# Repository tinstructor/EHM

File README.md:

# EHM
An energy harvester with advanced monitoring capabilities.

## Table of Contents
<!-- TOC -->

  - [About The Project](#about-the-project)
  - [Getting Started](#getting-started)
    - [Cloning the EHM Repository](#cloning-the-ehm-repository)
    - [Installing Autodesk EAGLE](#installing-autodesk-eagle)
    - [Navigating the Project Files](#navigating-the-project-files)
    - [Generating Gerber Files](#generating-gerber-files)
  - [Hardware Configuration](#hardware-configuration)
    - [Ordering PCB's](#ordering-pcbs)
    - [Sourcing Components](#sourcing-components)
    - [Soldering](#soldering)
  - [Device Operation](#device-operation)
    - [Energy Harvester](#energy-harvester)
    - [Current Sense Amplifiers](#current-sense-amplifiers)
    - [Voltage Buffer](#voltage-buffer)
    - [Power Delivery](#power-delivery)
    - [ADC](#adc)
    - [Solder Bridges](#solder-bridges)
  - [License](#license)

<!-- /TOC -->

## About The Project

This project was created with [Autodesk EAGLE](http://eagle.autodesk.com/)

## Getting Started

### Cloning the EHM Repository

In order to download the source files in a zip archive, click [here](https://github.com/tinstructor/EHM/archive/master.zip). Alternatively you may also clone this repository using git bash terminal commands. Substitute "John Doe" by your own username and use your own email address.

```bash
$ git config --global user.name "John Doe"
$ gif config --global user.email "john.doe@example.com"
```

Next up, enter the following command to clone the repository into the folder in which you opened the git bash terminal. Choose your location conveniently, for example `C:\Users\<username>\Documents\EAGLE\repos` might be a good place.

```bash
$ git clone https://github.com/tinstructor/EHM.git
```

From here on I'll assume all directies to be relative to whatever directory you chose to clone the project in. Also, I'll be using Windows style backslash notations because I just happened to be writing this on a Windows machine. If that offends you, you should really grow up.

### Installing Autodesk EAGLE

Once you've cloned the repository and thereby obtained the necessary files, a free version of Autodesk EAGLE may be downloaded from [here](https://www.autodesk.com/products/eagle/free-download). This is not some trial version that prompts you to spend money you really don't have, instead it is a limited version of the software meant for hobbyists. For our intents and purposes the features offered by the hobbyist version are more than adequate.

>**Note:** if you're a student or an educator you may apply for an educational license [here](https://www.autodesk.com/education/free-software/eagle), which grants you access to the full version of the latest EAGLE release, albeit for non-profit use only.

### Navigating the Project Files

When opening EAGLE for the first time, navigate to the `Options > Directories` tab in the top-left corner. A pop-up window will appear. It is here that you must now add the location of the project files in order to open them in EAGLE. Go to the `Projects` field and add the absolute location of the `EHM\Project` folder, seperating it from the default project location with a semicolon `;`.

The project files will now appear in the control panel view. Notice that there are 2 files present, i.e., a schematic and a board file. Double clicking either of these files will cause both of them to open simultaneously in a seperate window. It is imperative that you always have both file windows open at the same time when making changes of any type. Otherwise you may run into horrible inconsistency problems. No worries, if you where to accidently close one of these windows, EAGLE will prompt you with a bright yellow and black banner.

Learning to use EAGLE efficiently may seem difficult in the beginning but it's not actually that bad. In fact Autodesk has some nice [tutorials](https://www.autodesk.com/products/eagle/blog/?s=schematic+basics) that'll get you going in no time.

### Generating Gerber Files

In case you've made changes to the board layout, you'll need to generate new Gerber files. These files tell the machines of your PCB manufacturer of choice how to lay out all traces and other stuff exactly how you designed it. In order to do this, open the board layout window and navigate to the `File > CAM Processor` tab.

A pop-up window now appears. The process of generating gerber files is clearly demonstrated in [this video](https://youtu.be/Jf2y1rTRHDg). However, I've spared you some extra steps and created a simple cam job file `gerb274x.cam` (located in `EHM\CAM`) for you to load as follows:

After browsing the file explorer and choosing the appropriate CAM file, all you need to do is press the `Process Job` button in the bottom-right corner of the CAM Processor pop-up window. This will generate a new zip archive called `Gerber.zip` in the `EHM\Project` folder. If you didn't make any changes, a handy `Gerber.zip` archive is already located in the repository folder itself (`EHM\Gerber.zip`).

## Hardware Configuration

### Ordering PCB's

Now, when it comes to ordering PCB's there are a stupid amount of manufacturers out there and they're all claiming some perceived advantage over their competitors. Let me tell you, for the most part it's all marketing b\*llsh\*t. Which manufacturer you choose typically depends on price, manufacturing capabilities and how fast they can deliver. For hobbyists like you and me, the latter is typically of less importance while we tend to focuss more on low pricing.

These days, when I order relatively small dual-layer PCB's for prototyping purposes I'll typically order from [JLCPCB](https://jlcpcb.com/). For the price their manufacturing capabilities and quality are outstanding. In fact, you'll have a hard time finding better prices regardless off  manufacturing capabilities. I mean, €7.06 (before shipping) for 10 PCB's and a stencil is somewhat unreal.

>**Note:** choosing a lead-free finish will add €5.30 to the total price. However, since most hobbyist solder with leaded solder anyway, you must ask yourself whether shelling out extra money for a small batch of prototypes is worth it.

A great way to save some cost in the long run while making your job easier is to use a stencil printer like the [CYBRES SP2421](https://www.tindie.com/products/CYBRES/cybres-sp2421-stencil-printer/) or the [NeoDen PM3040](https://printtec.nl/contents/nl/d361.html). The purpose of a stencil printer will become clear in the section on [Soldering](#soldering). What you need to know at this stage is that there are two types of (manual) stencil printers: while the SP2421 requires no stencil frame (where the PM3040 does) it does require a set of precision cut holes in your stencil. If you've got the capabilities to cut these holes and do it precisely, it's a great way to save some money on both the printer itself as well as the additional shipping costs associated with framed stencils.

>**Note:** stencil jigs typically accept stencils with a maximum size. Make sure to set the size of the stencil accordingly when ordering! Setting a custom stencil size comes with no additional cost, at least on [JLCPCB](https://jlcpcb.com/) it doesn't.

### Sourcing Components

First of all, let me state that sourcing components for absolute bottom dollar (or euro in my case) may well be considered a black art. My advise would be to get what you can on [LCSC](https://lcsc.com/) and have them ship your order together with your PCB's from [JLCPCB](https://jlcpcb.com/). That way you can avoid additional shipping fees.

Since the component selection on LCSC is somewhat limited you could go to places like [Mouser](https://www.mouser.com/) for the miscellaneous stuff like the BQ25570RGRR energy harvesting IC and the MAX9934TAUA+ current sense amplifier.

~~Anyway, at the time of writing this, I wasn't sure yet as to which type of energy I'd be harvesting (solar, thermal, ...) so I couldn't really give you a Bill Of Materials (BOM).~~ However, since most critical components are marked in the schematic with their full partname I'm sure you'll have no trouble obtaining the correct components if you really wanted to. My advice would be to always make sure you get the part with the correct footprint.

>**Note:** make sure to order y14870rxxx00b9r type current resistors with a CSM2512 footprint as illustrated in `EHM\Datasheets\y14870rxxx00b9r.pdf`.

Oh yeah and before I forget, sites like [Banggood](https://www.banggood.com/) are amazing for getting pre-assembled cables like [this](https://www.banggood.com/100Pcs-Mini-Micro-JST-1_0mm-SH-2-Pin-Connector-Plug-With-Wires-Cables-150mm-p-1170285.html) one and [this](https://www.banggood.com/20Pcs-Mini-Micro-JST-1_0mm-SH-6-Pin-Connector-Plug-With-Wires-Cables-150mm-p-1170259.html) one. What's more, Banggood typically charges completely nothing for shipping. The only downside is that stuff will take some weeks to arrive at your doorstep. That's what you get for being so cheap.

### Soldering

While we're on the subject of Banggood, they have a pretty awesome selection of soldering supplies. I myself am a big fan of offerings from [Mechanic](https://www.banggood.com/search/mechanic-solder.html) and of their [XG-Z40](https://www.banggood.com/XG-Z40-10cc-Syringe-Solder-Paste-Flux-Paste-Sn63Pb37-25-45um-p-973158.html) solder paste syringe in particular. If you have no morality issues with leaded solder and you want to spend less money and time on soldering, XG-Z40 is the way to go.

>**Note:** when buying solder paste in a syringe (like the XG-Z40) you'll also need some [blunt tip needles](https://www.banggood.com/search/blunt-tip-fill-needle.html). Make sure to choose tips with a sufficiently large diameter. Otherwise you'll have a hard time pushing out solder paste. My advice is to go with 0.9mm diameter (typically pink) ones. You'll also need to plan a trip to your local pharmacy to get some [10ml syringes](https://www.farmaline.be/apotheek/bestellen/wegwerpspuit-10-ml-terumo-zonder-naald-ss-10es/) because you'll need the rubber plunger thingy in order to push the solder out of the syringe.

While XG-Z40 is fine for small rework purposes (as shown in [this](https://youtu.be/4Z1B_DbW-C0) video), when using a stencil you'd really need some [solder paste](https://www.banggood.com/MECHANIC-Soldering-Solder-Welding-Paste-Flux-SMD-SMT-Sn63Pb37-Tool-Soldering-Iron-Flux-Repair-Tool-p-1328894.html) in a jar. Numerous tutorials are available on how to start using stencils for solder paste dispension. For example [this](https://www.youtube.com/watch?v=WDIqtGMROjM) video from Sparkfun is a great place to start when you don't have the funds for an expensive stencil printer. If you do however (have such funds), [this](https://youtu.be/ud8odsM8eA4) video shows how its done.

After putting solder paste on your board and carefully sticking the component to it, you have several different options for heating the solder paste so that it may eventually solidify. For example, you could hit it with a [hot air station](https://www.reichelt.com/be/en/digital-hot-air-smd-rework-station-320w-esd-station-zd-939l-p161632.html). Hot air stations are relatively cheap compared to other solutions and besides, they are an irreplaceable shop tool. Another cheap-ish option is a [hot plate](https://www.tindie.com/products/LafrasH/modern-electronics-reflowr-v2/). The problem with it is that it really only works well for one side of your PCB, which would require you to manually solder components to the pads on the opposite side of the PCB with a hot air gun and/or a conventional soldering iron (with some special tips). Nonetheless this may prove useful if you've placed the most difficult to solder components on the same side. A much more powerful and vastly more expensive solution is something like a
[vapour phase reflow oven](https://www.eleshop.nl/vapour-phase-soldeeroven-mini-condens-it.html).

>**Note:** some people even use conventional electrically heated skillets or toaster ovens. While these methods are inexpensive, they tend to heat your PCB unevenly, potentially causing spotburns and/or tombstoning. The same can be said about the IR reflow ovens of yesteryear.

## Device Operation

### Energy Harvester

According to the design principles and other useful information laid out in `EHM\Datasheets\bq25570.pdf` and `EHM\Literature\sluuaa7a.pdf`, the BQ25570 IC allows for a number of configurations to be made pertaining to its operation. But before we can start you might be wondering, what exactly is the function of this chip? The following quote should start to make things somewhat clear:

> *"The bq25570 device is a highly integrated energy harvesting Nano-Power management solution that ... is specifically designed to efficiently acquire and manage the microwatts (µW) to milliwatts (mW) of power generated from a variety of DC sources like photovoltaic (solar) or thermal electric generators. \[It is\] targeted toward products and systems, such as wireless sensor networks (WSN) which have stringent power and operational demands."* <br/>
>
> **Texas Instruments**

In order to do this, the capabilities of the BQ25570 are twofold. First of all, it contains a boost charger whose intended purpose is to boost the low voltage output of harvesters such as small solar cells or a Thermo-Electric Generator (TEG) (connected to J2) to a constant voltage level that is sufficiently high to charge a storage element connected to the battery terminal J4. It does this as efficiently as possible by means of a mechanism called Maximum Powerpoint Tracking (MPPT). The purpose of MPPT is to match the input impedance of the boost charger to the output impedance of the energy harvester which in turn ensures a maximum transfer of power.

>**Note:** if you want to know more about how MPPT works I suggest you have a look at `EHM\Literature\erbay2014.pdf` and `EHM\Literature\kong2012.pdf`.

More specifically, in this case, the integrated MPPT block continuously measures a certain user configurable percentage (i.e., the MPPT percentage) of the energy harvester's open circuit voltage and uses this information to control the switching frequency of the boost converter to match its input impedance to be equal to the harvester's output impedance, thus assuring maximum power transfer. Choosing the MPPT percentage depends heavily on the type of energy harvesting device. If its output impedance is purely resistive, setting the MPPT percentage to 50% (VOC_SAMP = GND) ensures maximum power transfer. However, the capacitive nature of a solar cell's output impedance requires an MPPT percentage closer to 80% (VOC_SAMP = VBAT). For your convenience I've also added the possibility to set a custom MPPT percentage by means of a resistor divider consisting of (R20 + R21) and R22.

Switching the MPPT percentage between 50% (VOC_SAMP = GND), 80% (VOC_SAMP = VBAT) or a custom value can be done by setting a jumper (see picture below) to the corresponding position on JP1. The same connector (JP1) also provides the ability to either enable or disable the entire chip by tying the NEN input of the IC to GND or VBAT respectively.

That being said, certain requirements need to be met before the main boost charger (with the aforementioned impedance matching capabilities) is operational. More specifically, when VSTOR < VSTOR_CHGEN (= 1.8V) the IC operates in cold-start mode. The cold-start circuit is essentially an unregulated, hysteretic boost converter with lower efficiency compared to the main boost charger. None of the other features function during cold start operation.

>**Note:** `EHM\Literature\kong2012.pdf` explains in great detail why a cold start cirquit might be necessary.

The cold start circuit's goal is to charge the voltage on CSTOR (i.e., VSTOR) higher than VSTOR_CHGEN so that the main boost charger can operate. When the VSTOR voltage reaches VSTOR_CHGEN, the main boost charger starts up. Once the VSTOR pin voltage goes above VBAT_UV (1.95V) plus the VBAT_UV_HYST threshold (15mV), the VSTOR pin and VBAT pins are effectively shorted through an internal PMOS FET. The switch remains closed until the VSTOR pin voltage falls below the VBAT_UV threshold. The VBAT_UV threshold should be considered a fail safe to the system and the system load should be removed or reduced based on the user-configurable VBAT_OK threshold which should be set above the VBAT_UV threshold.

To prevent rechargeable batteries from being exposed to excessive charging voltages and to prevent over charging a capacitive storage element, the over-voltage (VBAT_OV) threshold level must be set using external resistors (see following equation). This is also the voltage value to which the charger will regulate the VSTOR/VBAT pin when the input provides sufficient power. The VBAT_OV threshold when the battery voltage is rising is given by:

The overvoltage threshold when battery voltage is decreasing is given by VBAT_OV minus VBAT_OV_HYST (24mV). Once the voltage at the battery exceeds the VBAT_OV threshold, the boost charger is disabled. The charger will start again once the battery voltage drops VBAT_OV_HYST.

The charger allows the user to set a programmable voltage independent of the overvoltage and undervoltage settings to indicate whether the VSTOR voltage (and therefore the VBAT voltage when the PFET between the two pins is turned on) is at an acceptable level. When the battery voltage is decreasing the threshold is set by:

When the battery voltage is increasing, the threshold is set by:

The logic high level of this signal (i.e., the VBAT_OK output) is equal to the VSTOR voltage and the logic low level is GND. Figure 21 taken from `EHM\Datasheets\bq25570.pdf` shows the relative position of the various threshold voltages discussed so far.

Anyway, apart from boosting the voltage of an energy harvester, the BQ25570 also contains a buck converter. The buck converter input is internally connected to VSTOR and steps the VSTOR voltage down to a lower regulated voltage at the OUT connector (J1 and J3). It employs pulse frequency modulation (PFM) control to regulate the voltage close to the desired reference voltage. The voltage regulated at the OUT pin is set by a user programmable resistor divider according to the following equation:

Connector JP2 allows you to configure the behaviour of the buck converter output. According to the BQ25570 datasheet (`EHM\Datasheets\bq25570.pdf`), if you tie VOUT_EN to VSTOR, the buck converter is disabled when the voltage on VSTOR drops below the VBAT_UV condition. The buck converter continues to operate in pass (100% duty cycle) mode, passing the input voltage to the output, as long as VSTOR is greater than VBAT_UV and less than VOUT. However, it fails to make clear the true functionality of the VOUT_EN input. You see, when reading `EHM\Literature\sluuaa7a.pdf`, it becomes evident that connecting VOUT_EN to VBAT_OK makes it so that the buck converter is turned off when VSTOR < VBAT_OK (when VSTOR is decreasing) or if VSTOR < VBAT_OK_HYST (when VSTOR increases). Connecting VOUT_EN to GND turns off the buck converter entirely.

The `EHM\BQ25570_Design_Help_V1_3.xlsx` spreadsheet is a handy tool that calculates a set of resistor values that fits best within the operational constraints provided by you, the user. For your convenience I've provided you with some values that reflect a common scenario wherein a single cel Li-Ion battery or a dual cell NiMH battery are used as a storage element in conjunction with, e.g., a small solar cell (with an output voltage ≤ 3.5V) such as [this](https://www.banggood.com/0_36W-2V-42_548_53mm-Solar-Panel-Epoxy-Board-with-Wire-p-1369156.html?rmmds=search&cur_warehouse=CN) one or [this](https://www.gearbest.com/other-accessories/pp_009728526124.html) one (when space is limited) or [this](https://www.banggood.com/3_5V-250mA-0_8W-Mini-Epoxy-Solar-Panel-Photovoltaic-Panel-p-987778.html?rmmds=search&cur_warehouse=CN) one when device footprint is no issue.

>**Note:** the MPPT percentage (40%) is just for demonstration purposes in this case. Solar panels work best when the MPPT percentage is set to approximately 80%.

Choosing an appropriately sized solar panel and storage element (most likely a 3.7V battery) is not an easy feat and depends heavily on your use case. Luckily I've provided another handy spreadsheet (`EHM\bq25570SolarAppDesignExample_V1p3.xlsx`) which accepts a number of parameters and calculates the required size of your solar panel as well as the minimum battery capacity required (given a nominal voltage). I've loaded the spreadsheet with some parameters that reflect the absolute worst case scenario for a sensor node that uses every possible function of the hardware (including chips other than the BQ25570) to repeatedly send a message every 60 seconds.

>**Note:** seriously, even if you tried you wouldn't be able to design a **sensor** node setup with a worse performance than the one laid out in `EHM\bq25570SolarAppDesignExample_V1p3.xlsx`. Except maybe if you used IEEE 802.11 links or something funny like that.

All resistors are E96 series 1% resistors with an 0603 footprint. The following table provides a summary of the proposed configuration and the passive components required:

I strongly recommend you to read `EHM\Datasheets\bq25570.pdf` for additional design considerations, e.g., regarding the appropriate sizing of several capacitors, etc.

### Current Sense Amplifiers

If the purpose is to monitor both input and output power, you'd need to measure both input and output current (as well as voltage). Hence, a shunt resistor was added to both the input and output, each in combination with a MAX9934TAUA Current Sense Amplifier (CSA). This device amplifies the voltage drop across the shunt resistance before it may be measured by an Analog to Digital Converter (ADC). If I hadn’t use a CSA, the voltage difference would either be too small to measure or you'd need to make the shunt resistor very big, leading to unacceptable power losses.

The MAX9934TAUA is an interesting CSA in that it behaves as a current-source with a transconductance . Thus, by pulling its output to GND with a sufficiently large resistor (let's call it  for now) we are able to adjust the voltage gain  according to the following equation:

Let's say you'd want to use an ADC with a resolution of 10 bits. At this resolution there are  levels ranging from 0V to the VOUT of the buck converter (2.7V if you used the proposed configuration). The following equation shows how one could calculate the measured voltage given an output value x of the ADC:

In our case, the smallest measurable voltage delta (by the ADC) equals . Now, assume we want to measure the current through the input shunt resistor with a resolution of 200µA, then the smallest possible voltage gain may be obtained from the following equation:

However since the ADC input only ranges to VOUT of the buck converter, there's also a maximum possible voltage gain. Let's say the maximum input current of the boost charger equals 200mA (which is well within the specs stated in `EHM\Datasheets\bq25570.pdf`), then the following equation puts an upper limit to the voltage gain:

>**Note:** you could easily calculate that in fact, the shunt resistor is not the limiting factor when it comes to resolution. In all cases  must hold true. By assuming the resolution is unknown this comes down to: <br/>
>
>  <br/>
>
> 

A trade-off now presents itself. The larger the shunt resistance, the lower the voltage gain and the less influence small (tolerance) deviations have on the measurement. However, a larger shunt resistor also equates to more power loss. Let's say that a shunt resistor of 50mΩ does the trick. Assuming the measurement resolution equals 200µA, the voltage gain must be somewhere in the range of . The corresponding output termination resistor () can then be calculated as follows:

Therefore . I strongly encourage the use of a 10.7kΩ 0.1% 0603 resistor like the one found in `EHM\Datasheets\era-3aeb1072v.pdf`. This offering from Panasonic is extremely precise. In that case the voltage gain equates to:

>**Note:** calculating the current is now simply a matter of dividing a measurement obtained from the ADC by the known gain and shunt resistor values (in software).

The output shunt resistor employs the same principles. However, according to `EHM\Datasheets\bq25570.pdf`, the maximum output current of the buck converter equals 110mA. Therefore, the following equation must hold true:

Again, in all cases  must hold true. By assuming the resolution to be an unknown variable x this comes down to:

 <br/>

Let's say a resolution of 110µA is adequate for our purposes and a shunt resistor of 100mΩ does the trick. Then, the voltage gain must be somewhere in the range of . Thus . I strongly encourage the use of a 9.76kΩ 0.1% 0603 resistor like the one found in `EHM\Datasheets\era-3aeb9761v.pdf`. This offering from Panasonic is extremely precise. In that case the voltage gain equates to:

>**Note:** due to footprint requirements, the only possible shunt resistors are specified in `EHM\Datasheet\y14870rxxx00b9r.pdf`. For example, in the above case, you'd need to order the Y14870R10000B9R and Y14870R05000B9R variants.

For your convenience I've added a spreadsheet in `EHM\CSA_help.xlsx` that combines all these calculations. This allows you to properly configure your current sense amplifiers based on the precision of your ADC (expressed as N bits) as well as the transconductance of the CSA and the output voltage (i.e., the positive rail of the ADC) of the bq25570 buck converter output. For example (see image below), with a 12 bit ADC one could increase the current measurement resolution significantly, at the cost of increased power consumption inherent to a more precise ADC that is. 

### Voltage Buffer

The input resistance and capacitance of an ADC input are typically chosen to accomodate most common scenarios. However, when dealing with particularly small currents and voltages it is common to buffer these inputs for all sorts of reasons. Moreover, it is considered good practice to filter out spurious high frequency compoments at the ADC inputs because otherwise they might be replicated in the frequency spectrum after sampling and distort your measurements (think Shannon-Nyquist theorem). According to the principles laid out in `EHM\Literature\tidu390.pdf` and the information obtained from `EHM\Datasheets\ads7041.pdf`, a buffer-filter combination consisting of an `EHM\Datasheets\opa314.pdf` op-amp and low pass RC filter with  and  was chosen.

>**Note:** both `EHM\Literature\tidu390.pdf` and `EHM\Datasheets\ads7041.pdf` stress the importance of using an NOG type ceramic capacitor for  over a common XR7 type capacitor since these may yield spurious frequency harmonics due to the fact that their actual capacitance value is typically temperature dependent.

>**Note:** since , the sampling rate should be at least 1 MSPS in order to comply with the Shannon-Nyquist sampling theorem, and ideally even higher since no analog filter is infinitely steep.

All signals that are to be sampled are multiplexed onto a single line just before the buffer-filter input with a `EHM\Datasheets\dg2034e.pdf` low rds-on 4 channel MUX. Since the input impedance of the buffer is very high, the additional resistance introduced by the MUX shouldn't result in significant attenuation of the signals. The following thruth table lists which input (denoted with S) is switched to the output according to the logical signal level on the A0 and A1 inputs.

When properly configured (by means of the appropriate solder bridges) S1 is connected to the (divided) input signal  of the bq25570 boost charger, i.e., the positive terminal of connector J2. In similar fashion, S2 is connected to the (divided) positive output of the connected storage element  while S3 is connected to the output of the CSA measuring the bq25570 buck converter output current and S4 is connected to the output of the CSA measuring the bq25570 boost charger input current. The following image shows the location of connector J7, which contains the A0 and A1 inputs. 

Because the battery and input voltage may be greater than the MUX, buffer and ADC supply voltage, I've added the possibility to divide the corresponding MUX input voltages by means of a resistor divider. It is advisable to go with large resistance values so as to minimize power losses. Something like the 10MΩ 0.5% 0603 resistors from `EHM\Datasheets\crcw060310m0dheap.pdf` are an exellent choice.

### Power Delivery

Coming soon

### ADC

Coming soon

### Solder Bridges

Coming soon

## License
This project and all original material included with it are released under [CC BY-SA 3.0](https://creativecommons.org/licenses/by-sa/3.0/)

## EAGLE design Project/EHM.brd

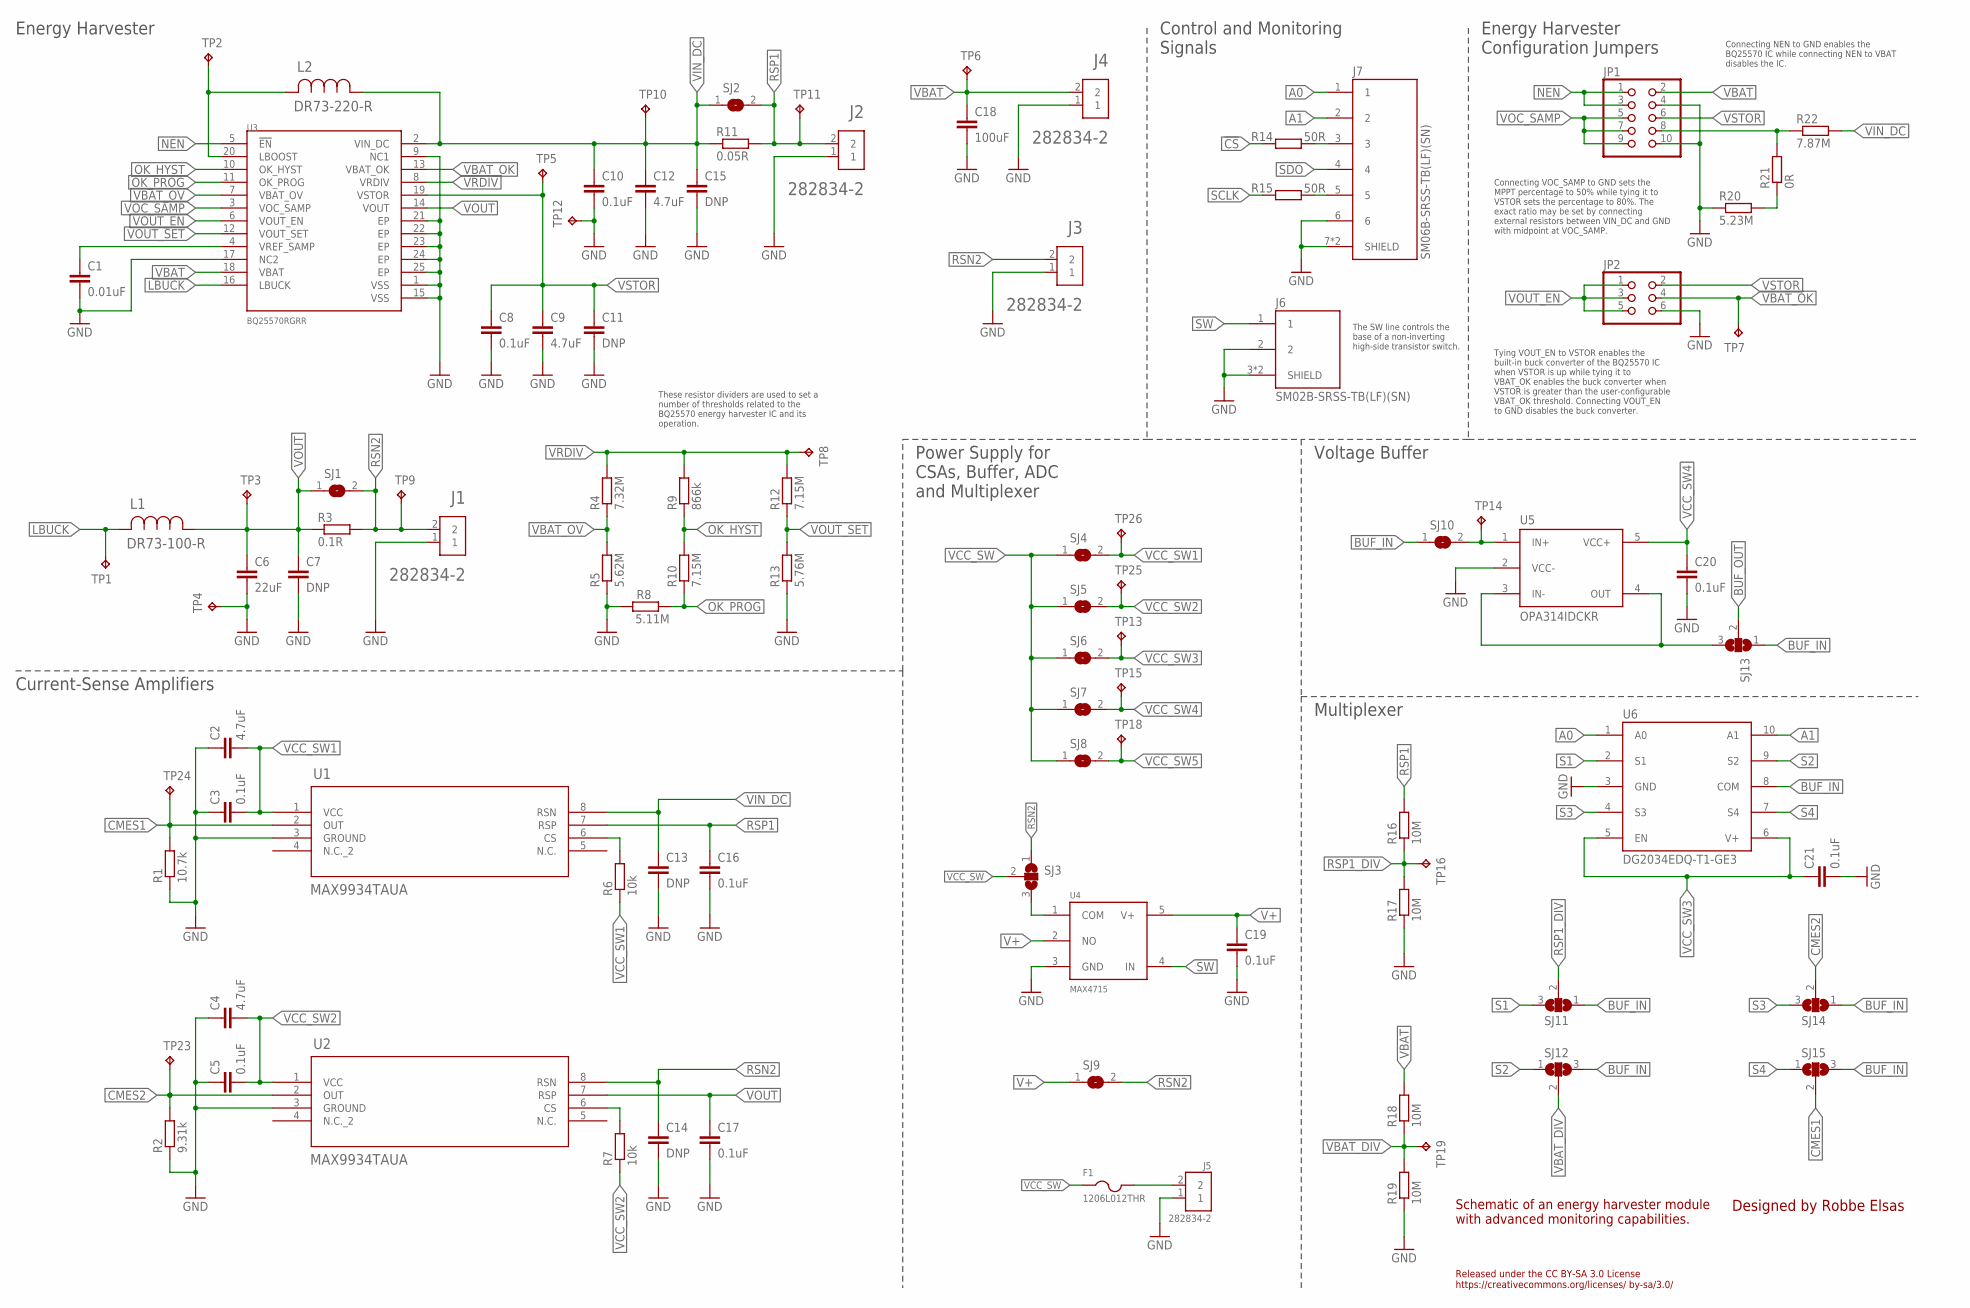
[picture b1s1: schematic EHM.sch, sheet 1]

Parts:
C1: 0.01uF; C0805
C2, C4, C9, C12: 4.7uF; C0805
C3, C5, C8, C10, C16, C17, C19, C20, C21: 0.1uF; C0805
C6: 22uF; C0805
C7, C11, C13, C14, C15: DNP; C0805
C18: 100uF; C1210
F1: 1206L012THR; R1206
J1, J2, J3, J4, J5: 282834-2; CONN_282834-2
J6: SM02B-SRSS-TB(LF)(SN); SM02B-SRSS-TB
J7: SM06B-SRSS-TB(LF)(SN); SM06B-SRSS-B
JP1: PINHD-2X5; 2X05
JP2: PINHD-2X3; 2X03
L1: DR73-100-R; DR73
L2: DR73-220-R; DR73
R1: 10.7k; R0603
R2: 9.31k; R0603
R3: 0.1R; Y14870RXX000B9R
R4: 7.32M; R0603
R5: 5.62M; R0603
R6, R7: 10k; R0603
R8: 5.11M; R0603
R9: 866k; R0603
R10, R12: 7.15M; R0603
R11: 0.05R; Y14870RXX000B9R
R13: 5.76M; R0603
R14, R15: 50R; R0603
R16, R17, R18, R19: 10M; R0603
R20: 5.23M; R0603
R21: 0R; R0603
R22: 7.87M; R0603
SJ1, SJ2, SJ4, SJ5, SJ6, SJ7, SJ8, SJ9, SJ10: SJ
SJ3, SJ11, SJ12, SJ13, SJ14, SJ15: SJ2W; SJ_2
TP1, TP4, TP6, TP7, TP8, TP11, TP12, TP16, TP19, TP23, TP24: TPPAD1-13; P1-13
TP2, TP3, TP5, TP9, TP10, TP13, TP14, TP15, TP18, TP25, TP26: TPB1,27; B1,27
U1, U2: MAX9934TAUA; 21-0036K
U3: BQ25570RGRR; QFN50P350X350X100-21N
U4: MAX4715; SC70-5L
U5: OPA314IDCKR; SC70-5L
U6: DG2034EDQ-T1-GE3; MSOP10

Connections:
!CS!: R14.1; also elsewhere on the board
A0: J7.1, U6.1 (A0)
A1: J7.2, U6.10 (A1)
BUF_IN: SJ10.1, SJ11.1, SJ12.3, SJ13.1, SJ14.1, SJ15.3, U6.8 (COM)
BUF_OUT: SJ13.2; also elsewhere on the board
CMES1: R1.2, SJ15.2, TP24.TP, U1.2 (OUT)
CMES2: R2.2, SJ14.2, TP23.TP, U2.2 (OUT)
GND: C1.2, C2.1, C3.1, C4.1, C5.1, C6.2, C7.2, C8.2, C9.2, C10.2, C11.2, C12.2, C13.2, C14.2, C15.2, C16.2, C17.2, C18.2, C19.2, C20.2, C21.2, J1.1, J2.1, J3.1, J4.1, J5.1, J6.2, J6.3 (SHIELD), J6.4 (SHIELD), J7.6, J7.7 (SHIELD), J7.8 (SHIELD), JP1.4, JP1.10, JP2.6, R1.1, R2.1, R5.1, R8.1, R13.1, R17.1, R19.1, R20.1, TP4.TP, TP12.TP, U1.3 (GROUND), U2.3 (GROUND), U3.1 (VSS), U3.9 (NC1), U3.15 (VSS), U3.17 (NC2), U3.21 (EP), U3.22 (EP), U3.23 (EP), U3.24 (EP), U3.25 (EP), U4.3 (GND), U5.2 (VCC-), U6.3 (GND); also elsewhere on the board
LBOOST: L2.2, TP2.TP, U3.20 (LBOOST)
LBUCK: L1.2, TP1.TP, U3.16 (LBUCK)
unnamed: R20.2, R21.1
unnamed: JP1.8, R21.2, R22.1
unnamed: R6.2, U1.6 (CS)
unnamed: F1.2, J5.2
unnamed: R7.2, U2.6 (CS)
unnamed: SJ10.2, TP14.TP, U5.1 (IN+)
unnamed: J7.3, R14.2
unnamed: SJ3.3, U4.1 (COM)
unnamed: J7.5, R15.2
unnamed: SJ13.3, U5.3 (IN-), U5.4 (OUT)
NEN: JP1.1, JP1.3, U3.5 (!EN)
OK_HYST: R9.1, R10.2, U3.10 (OK_HYST)
OK_PROG: R8.2, R10.1, U3.11 (OK_PROG)
RSN2: C14.1, J1.2, J3.2, R3.P$3 (2), R3.P$4 (2), SJ1.2, SJ3.1, SJ9.2, TP9.TP, U2.8 (RSN)
RSP1: C16.1, J2.2, R11.P$3 (2), R11.P$4 (2), R16.2, SJ2.2, TP11.TP, U1.7 (RSP)
RSP1_DIV: R16.1, R17.2, SJ11.2, TP16.TP
S1: SJ11.3, U6.2 (S1)
S2: SJ12.1, U6.9 (S2)
S3: SJ14.3, U6.4 (S3)
S4: SJ15.1, U6.7 (S4)
SCLK: R15.1; also elsewhere on the board
SDO: J7.4; also elsewhere on the board
SW: J6.1, U4.4 (IN)
V+: C19.1, SJ9.1, U4.2 (NO), U4.5 (V+)
VBAT: C18.1, J4.2, JP1.2, R18.2, TP6.TP, U3.18 (VBAT)
VBAT_DIV: R18.1, R19.2, SJ12.2, TP19.TP
VBAT_OK: JP2.4, TP7.TP, U3.13 (VBAT_OK)
VBAT_OV: R4.1, R5.2, U3.7 (VBAT_OV)
VCC_SW: F1.1, SJ3.2, SJ4.1, SJ5.1, SJ6.1, SJ7.1, SJ8.1
VCC_SW1: C2.2, C3.2, R6.1, SJ4.2, TP26.TP, U1.1 (VCC)
VCC_SW2: C4.2, C5.2, R7.1, SJ5.2, TP25.TP, U2.1 (VCC)
VCC_SW3: C21.1, SJ6.2, TP13.TP, U6.5 (EN), U6.6 (V+)
VCC_SW4: C20.1, SJ7.2, TP15.TP, U5.5 (VCC+)
VCC_SW5: SJ8.2, TP18.TP; also elsewhere on the board
VIN_DC: C10.1, C12.1, C13.1, C15.1, L2.1, R11.P$1 (1), R11.P$2 (1), R22.2, SJ2.1, TP10.TP, U1.8 (RSN), U3.2 (VIN_DC)
VOC_SAMP: JP1.5, JP1.7, JP1.9, U3.3 (VOC_SAMP)
VOUT: C6.1, C7.1, C17.1, L1.1, R3.P$1 (1), R3.P$2 (1), SJ1.1, TP3.TP, U2.7 (RSP), U3.14 (VOUT)
VOUT_EN: JP2.1, JP2.3, JP2.5, U3.6 (VOUT_EN)
VOUT_SET: R12.1, R13.2, U3.12 (VOUT_SET)
VRDIV: R4.2, R9.2, R12.2, TP8.TP, U3.8 (VRDIV)
VREF_SAMP: C1.1, U3.4 (VREF_SAMP)
VSTOR: C8.1, C9.1, C11.1, JP1.6, JP2.2, TP5.TP, U3.19 (VSTOR)

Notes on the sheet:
Released under the CC BY-SA 3.0 License https://creativecommons.org/licenses/ by-sa/3.0/
Schematic of an energy harvester module with advanced monitoring capabilities.
Designed by Robbe Elsas
Voltage Buffer
Current-Sense Amplifiers
Power Supply for CSAs, Buffer, ADC and Multiplexer
Control and Monitoring Signals
Energy Harvester
Energy Harvester Configuration Jumpers
The SW line controls the base of a non-inverting high-side transistor switch.
Connecting NEN to GND enables the BQ25570 IC while connecting NEN to VBAT disables the IC.
Connecting VOC_SAMP to GND sets the MPPT percentage to 50% while tying it to VSTOR sets the percentage to 80%. The exact ratio may be set by connecting external resistors between VIN_DC and GND with midpoint at VOC_SAMP.
Tying VOUT_EN to VSTOR enables the built-in buck converter of the BQ25570 IC when VSTOR is up while tying it to VBAT_OK enables the buck converter when VSTOR is greater than the user-configurable VBAT_OK threshold. Connecting VOUT_EN to GND disables the buck converter.
These resistor dividers are used to set a number of thresholds related to the BQ25570 energy harvester IC and its operation.
Multiplexer

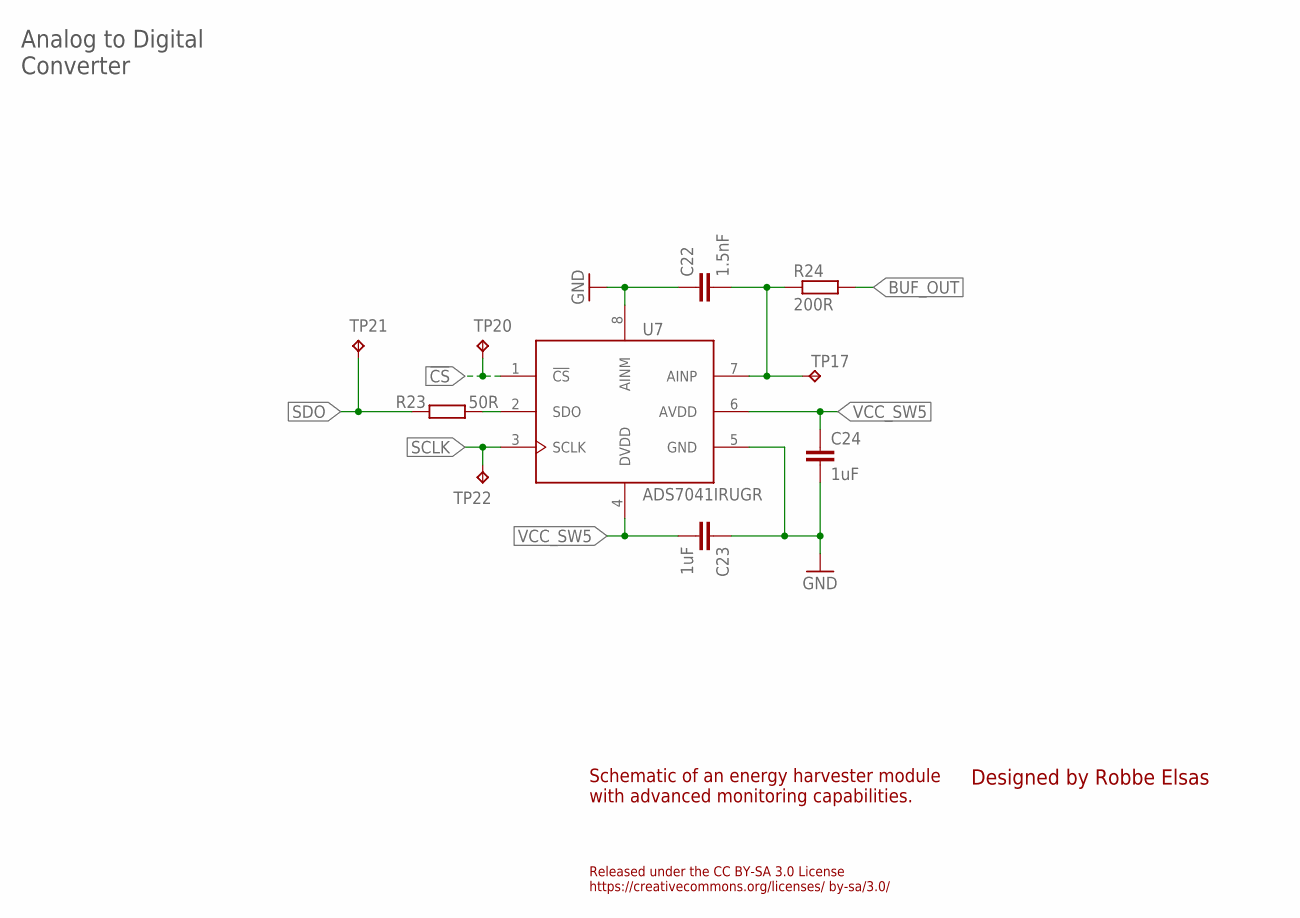
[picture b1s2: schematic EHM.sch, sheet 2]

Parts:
C22: 1.5nF; C0603
C23, C24: 1uF; C0805
R23: 50R; R0603
R24: 200R; R0603
TP17, TP20, TP21, TP22: TPB1,27; B1,27
U7: ADS7041IRUGR; QFN50P150X150X40-8N

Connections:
!CS!: TP20.TP, U7.1 (!CS!); also elsewhere on the board
BUF_OUT: R24.2; also elsewhere on the board
GND: C22.1, C23.1, C24.2, U7.5 (GND), U7.8 (AINM); also elsewhere on the board
unnamed: R23.2, U7.2 (SDO)
unnamed: C22.2, R24.1, TP17.TP, U7.7 (AINP)
SCLK: TP22.TP, U7.3 (SCLK); also elsewhere on the board
SDO: R23.1, TP21.TP; also elsewhere on the board
VCC_SW5: C23.2, C24.1, U7.4 (DVDD), U7.6 (AVDD); also elsewhere on the board

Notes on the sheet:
Designed by Robbe Elsas
Schematic of an energy harvester module with advanced monitoring capabilities.
Released under the CC BY-SA 3.0 License https://creativecommons.org/licenses/ by-sa/3.0/
Analog to Digital Converter

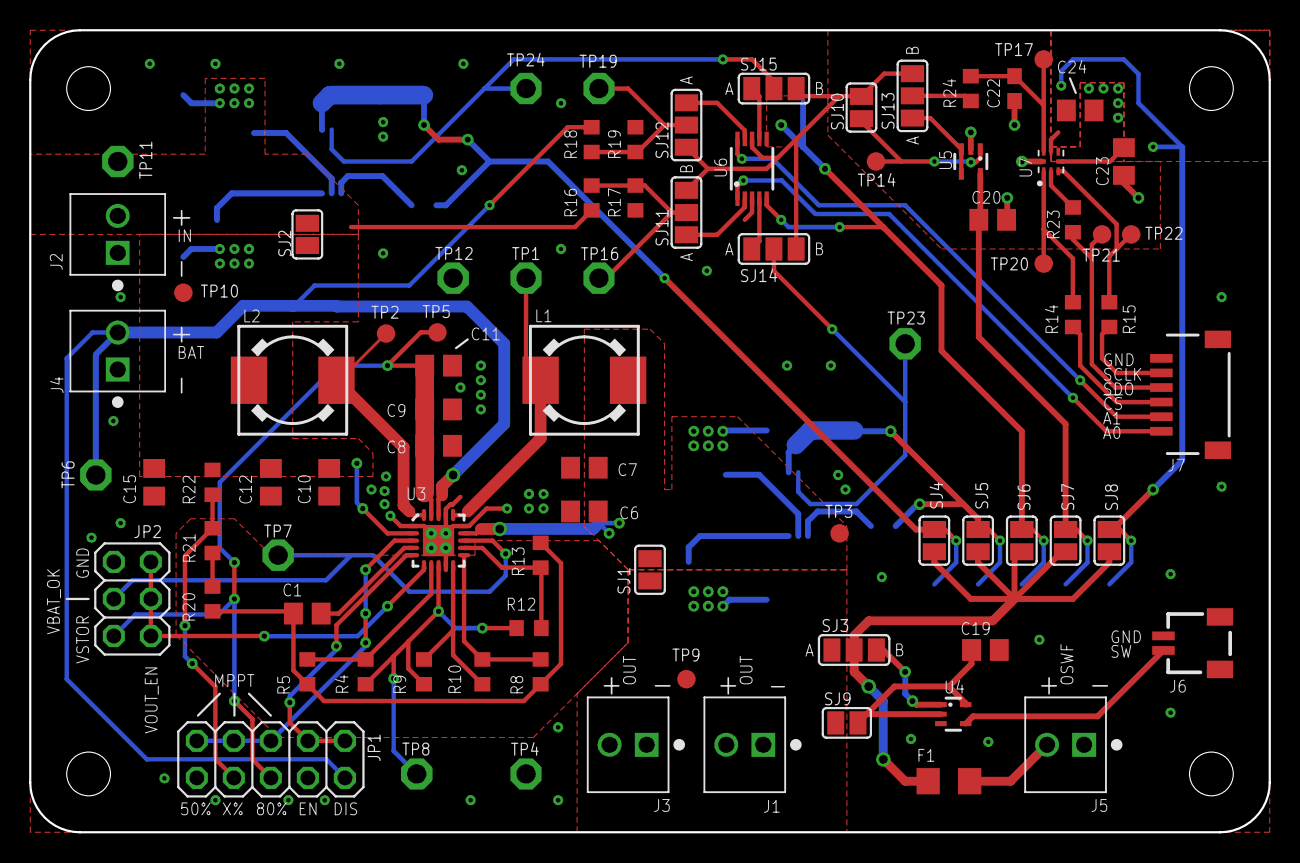
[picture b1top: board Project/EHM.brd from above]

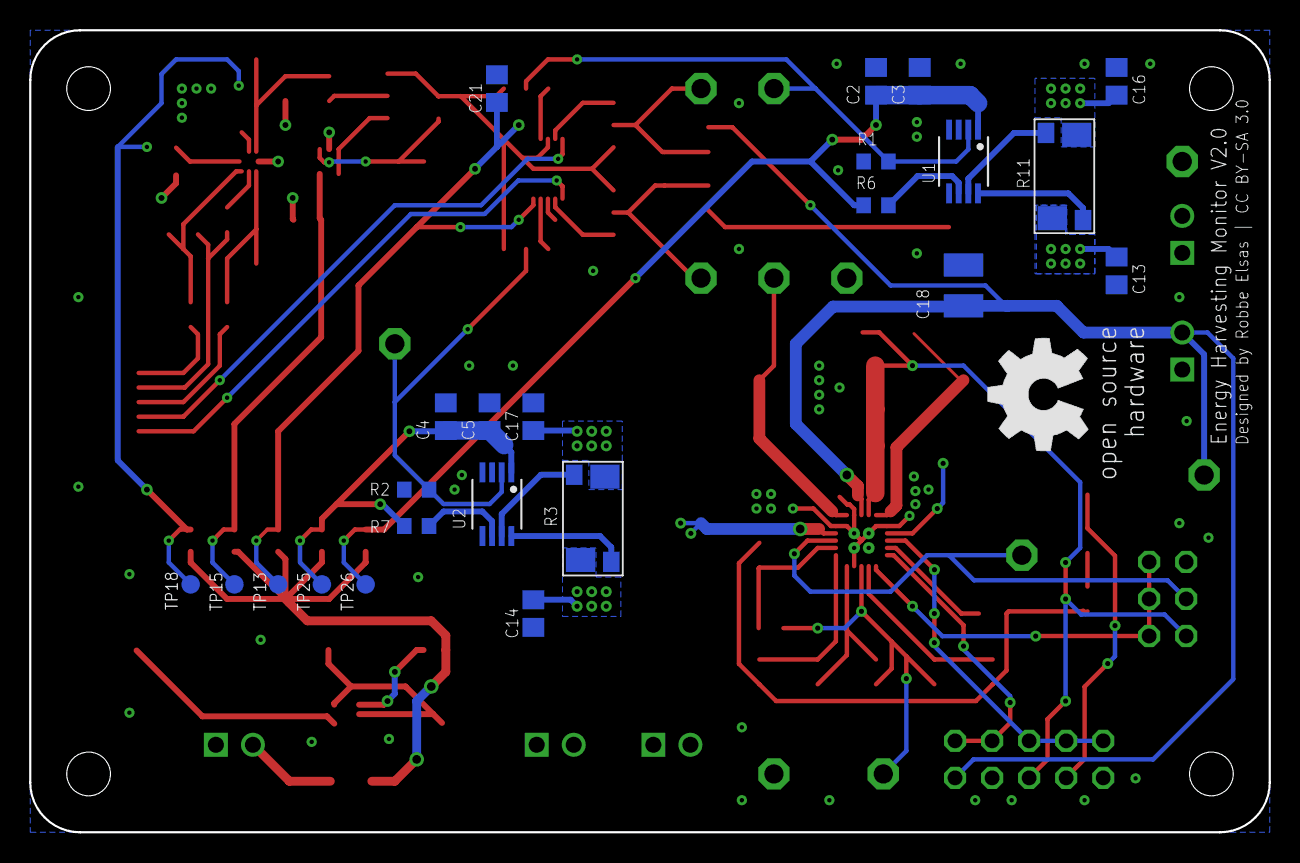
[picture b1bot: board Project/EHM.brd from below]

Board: 2 copper layers, 85.0 x 55.0 mm, 109 parts (24 on the bottom side), 54 nets.

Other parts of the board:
U$1: OSHW_8MM

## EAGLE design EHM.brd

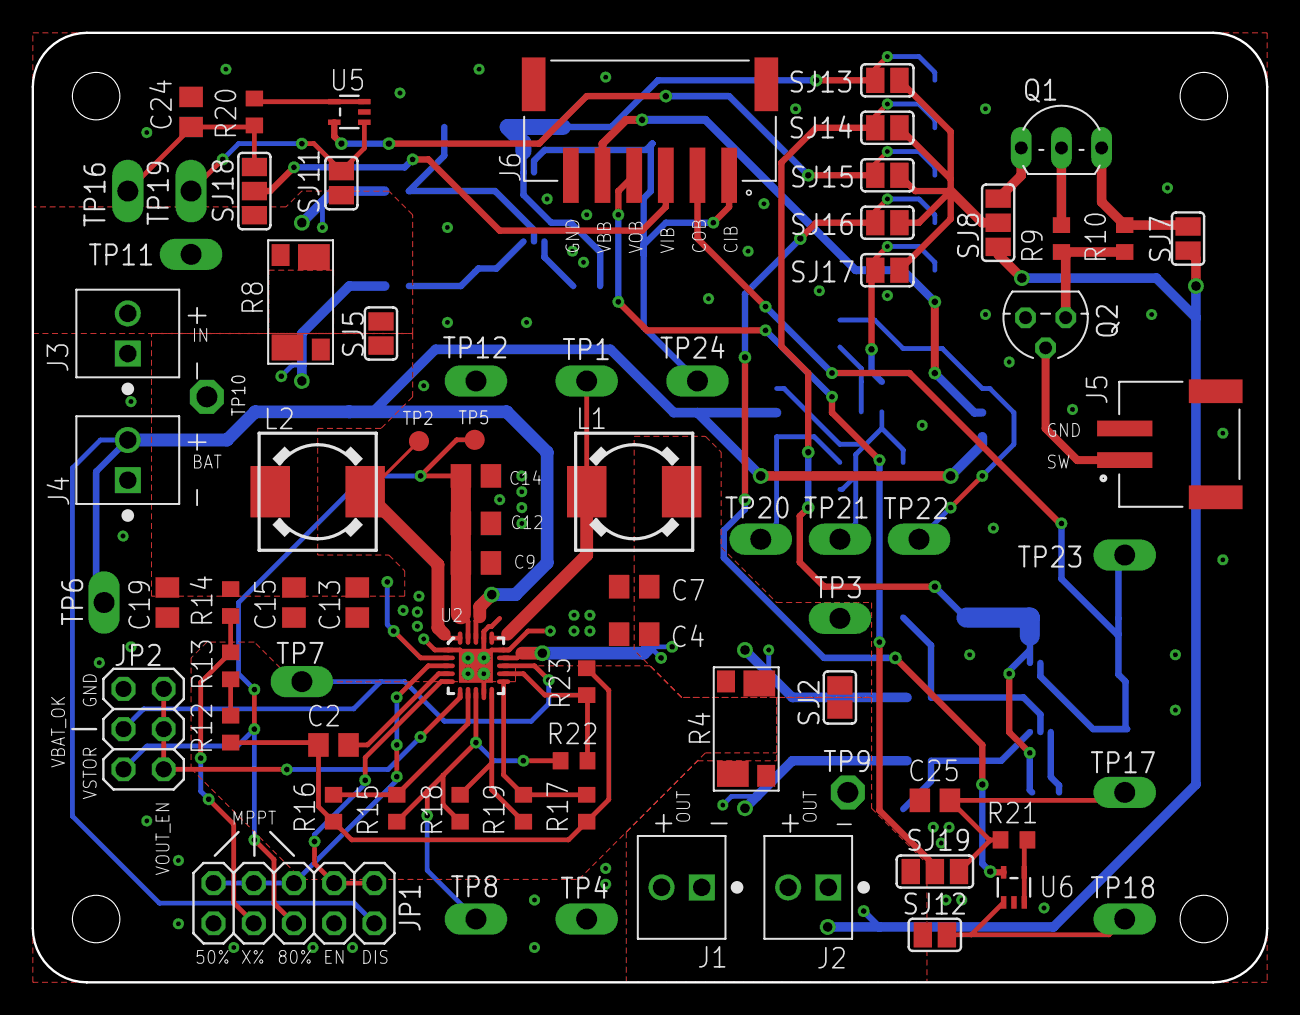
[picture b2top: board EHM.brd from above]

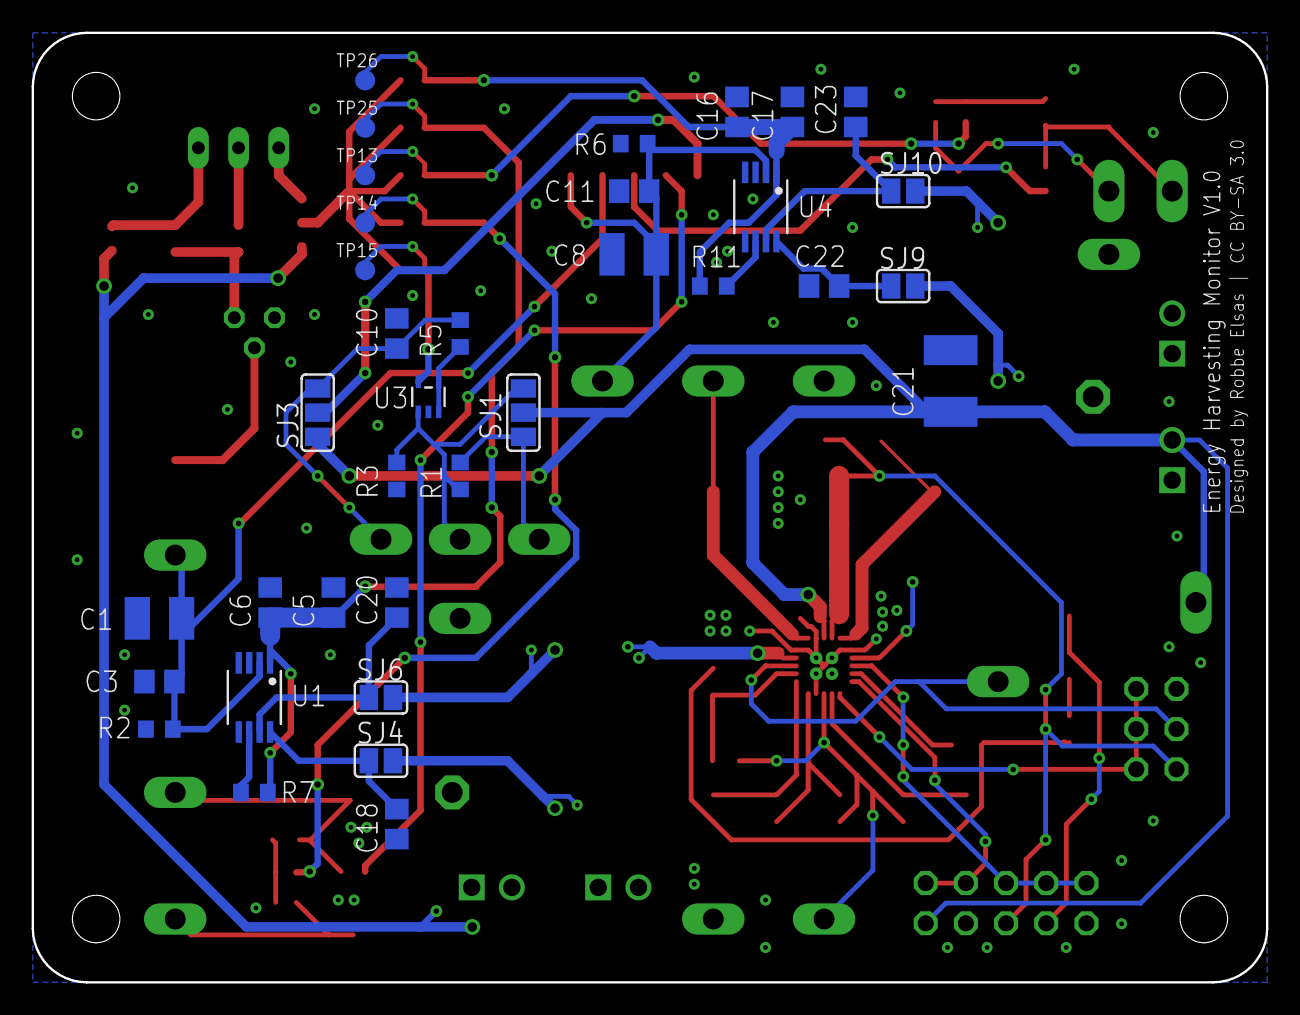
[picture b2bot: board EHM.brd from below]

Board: 2 copper layers, 78.0 x 60.0 mm, 111 parts (35 on the bottom side), 53 nets.

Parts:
C1, C8: DNP; C1210
C2, C3, C11: 0.01uF; C0805
C4: 22uF; C0805
C5, C12, C15, C16: 4.7uF; C0805
C6, C9, C13, C17, C20, C23: 0.1uF; C0805
C7, C14, C18, C19, C22: DNP; C0805
C10, C24, C25: C0805
C21: DNP; C1812
J1, J2, J3, J4: 282834-2; CONN_282834-2
J5: S2B-PH-SM4-TB(LF)(SN); JST_S2B-PH-SM4-TB(LF)(SN)
J6: S6B-PH-SM4-TB(LF)(SN); JST_S6B-PH-SM4-TB(LF)(SN)
JP1: 2X05
JP2: 2X03
L1: DR73-100-R; DR73
L2: DR73-220-R; DR73
Q1: BC557B; TO92-EBC
Q2: BC547B; TO92
R1, R3, R5, R7, R9, R10, R11, R12, R13, R14, R20, R21: DNP; R0603
R2, R6, R15, R16, R17, R18, R19, R22, R23: R0603
R4, R8: Y14870RXX000B9R
SJ1, SJ3, SJ8, SJ18, SJ19: SJ_2
SJ2, SJ4, SJ5, SJ6, SJ7, SJ9, SJ10, SJ11, SJ12, SJ13, SJ14, SJ15, SJ16, SJ17: SJ
TP1, TP3, TP4, TP6, TP7, TP8, TP11, TP12, TP16, TP17, TP18, TP19, TP20, TP21, TP22, TP23, TP24: TPPAD1-13Y; P1-13Y
TP2, TP5, TP13, TP14, TP15, TP25, TP26: TPB1,27; B1,27
TP9, TP10: TPPAD1-13; P1-13
U1, U4: MAX9934TAUA; 21-0036K
U2: BQ25570RGRR; QFN50P350X350X100-21N
U3, U5, U6: TSU111ICT; SC70-5

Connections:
CMES1: C8.1, C11.1, J6.1, R6.2, TP24.TP, U4.2
CMES2: C1.1, C3.1, J6.2, R2.2, TP23.TP, U1.2
GND: C1.2, C2.2, C3.2, C4.2, C5.1, C6.1, C7.2, C8.2, C9.2, C10.2, C11.2, C12.2, C13.2, C14.2, C15.2, C16.1, C17.1, C18.2, C19.2, C20.2, C21.2, C22.2, C23.2, C24.2, C25.2, J1.1, J2.1, J3.1, J4.1, J5.2, J5.S1, J5.S2, J6.6, J6.S1, J6.S2, JP1.4, JP1.10, JP2.6, Q2.1, R2.1, R3.1, R6.1, R12.1, R16.1, R17.1, R23.1, TP4.TP, TP12.TP, U1.3, U2.1, U2.9, U2.15, U2.17, U2.21, U2.22, U2.23, U2.24, U2.25, U3.2, U4.3, U5.2, U6.2
LBOOST: L2.2, TP2.TP, U2.20
LBUCK: L1.2, TP1.TP, U2.16
unnamed: C22.1, SJ9.1, U4.8
unnamed: R12.2, R13.1
unnamed: JP1.8, R13.2, R14.1
unnamed: R11.2, U4.6
unnamed: R20.1, U5.3, U5.4
unnamed: C23.1, SJ10.1, U4.7
unnamed: R7.2, U1.6
unnamed: SJ11.2, TP19.TP, U5.1
unnamed: R21.1, U6.3, U6.4
unnamed: C20.1, SJ6.1, U1.7
unnamed: C18.1, SJ4.1, U1.8
unnamed: C24.1, R20.2, SJ18.3, TP16.TP
unnamed: C25.1, R21.2, SJ19.3, TP17.TP
unnamed: SJ12.2, TP18.TP, U6.1
unnamed: R5.1, U3.3, U3.4
unnamed: C10.1, R5.2, SJ3.3, TP22.TP
unnamed: R1.2, R3.2, SJ1.1, TP21.TP, U3.1
unnamed: R1.1, SJ1.3, TP20.TP
unnamed: Q2.3, R9.1, R10.2
unnamed: Q1.B, R9.2
unnamed: Q1.C, SJ8.3
unnamed: Q1.E, R10.1, SJ7.2
NEN: JP1.1, JP1.3, U2.5
OK_HYST: R18.1, R19.2, U2.10
OK_PROG: R17.2, R19.1, U2.11
RSN2: J1.2, J2.2, R4.P$3, R4.P$4, SJ2.2, SJ4.2, SJ7.1, SJ8.1, SJ12.1, SJ19.1, TP9.TP
RSN2_BUF: J6.4, SJ19.2
RSP1: J3.2, R8.P$3, R8.P$4, SJ5.2, SJ10.2, SJ11.1, SJ18.1, TP11.TP
RSP1_BUF: J6.3, SJ18.2
SW: J5.1, Q2.2
VBAT: C21.1, J4.2, JP1.2, SJ1.2, SJ3.1, TP6.TP, U2.18
VBAT_BUF: J6.5, SJ3.2
VBAT_OK: JP2.4, TP7.TP, U2.13
VBAT_OV: R15.1, R16.2, U2.7
VCC_SW: SJ8.2, SJ13.1, SJ14.1, SJ15.1, SJ16.1, SJ17.1
VCC_SW1: C16.2, C17.2, R11.1, SJ13.2, TP26.TP, U4.1
VCC_SW2: C5.2, C6.2, R7.1, SJ14.2, TP25.TP, U1.1
VCC_SW3: SJ15.2, TP13.TP, U5.5
VCC_SW4: SJ16.2, TP14.TP, U6.5
VCC_SW5: SJ17.2, TP15.TP, U3.5
VIN_DC: C13.1, C15.1, C19.1, L2.1, R8.P$1, R8.P$2, R14.2, SJ5.1, SJ9.2, TP10.TP, U2.2
VOC_SAMP: JP1.5, JP1.7, JP1.9, U2.3
VOUT: C4.1, C7.1, L1.1, R4.P$1, R4.P$2, SJ2.1, SJ6.2, TP3.TP, U2.14
VOUT_EN: JP2.1, JP2.3, JP2.5, U2.6
VOUT_SET: R22.1, R23.2, U2.12
VRDIV: R15.2, R18.2, R22.2, TP8.TP, U2.8
VREF_SAMP: C2.1, U2.4
VSTOR: C9.1, C12.1, C14.1, JP1.6, JP2.2, TP5.TP, U2.19

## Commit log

2018-12-05 Added relevant datasheets
2018-12-05 Added relevant literature
2018-12-05 Changed op-amps and added decoupling cap
2018-12-05 Updated Gerber files to reflect changes in board layout
2018-12-10 Update README.md and add BQ25570 design help
2018-12-11 Added current sense resistor datasheet
2018-12-11 Update README.md and add some literature on MPPT
2018-12-12 Add solar app design example and update README.md
2018-12-12 Update README.md and change solar app values
2018-12-14 Added resistor to base of high side switch
2018-12-14 Update README.md and add datasheet for CSA termination resistor
2018-12-14 Update README.md and add datasheet
2018-12-14 Updated to V1.4
2019-01-13 First commit to develop branch
2019-01-18 Changed power delivery + swapped buffers for single buffer + SPI ADC
2019-01-18 Added gitignore
2019-01-18 Updated gitignore to ignore library backup files
2019-01-19 Updated README.md (partially) + support files
2019-01-19 Fixed imgur link
2019-01-19 Updated schematic pdf files
2019-01-19 Deleted old libraries
2019-01-19 Added CSA design helper
2019-01-19 Added OSHW logo
2019-01-19 Updated GERBER files
2019-01-20 Updated README.md + gerber files
2019-01-20 Remove redundant literature + update README.md
2019-01-20 Added notice of NOG type MLCC to README.md
2019-01-20 Fixed link to Voltage Buffer title
2019-01-20 New link fix

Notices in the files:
README.md:
License:
This project and all original material included with it are released under [CC BY-SA 3.0](https://creativecommons.org/licenses/by-sa/3.0/)
EHM.brd:
Designed by Robbe Elsas | CC BY-SA 3.0
